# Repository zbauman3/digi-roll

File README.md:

# DigiRoll

A digital dice roller for D&D. Check out the docs site at https://zbauman3.github.io/digi-roll/

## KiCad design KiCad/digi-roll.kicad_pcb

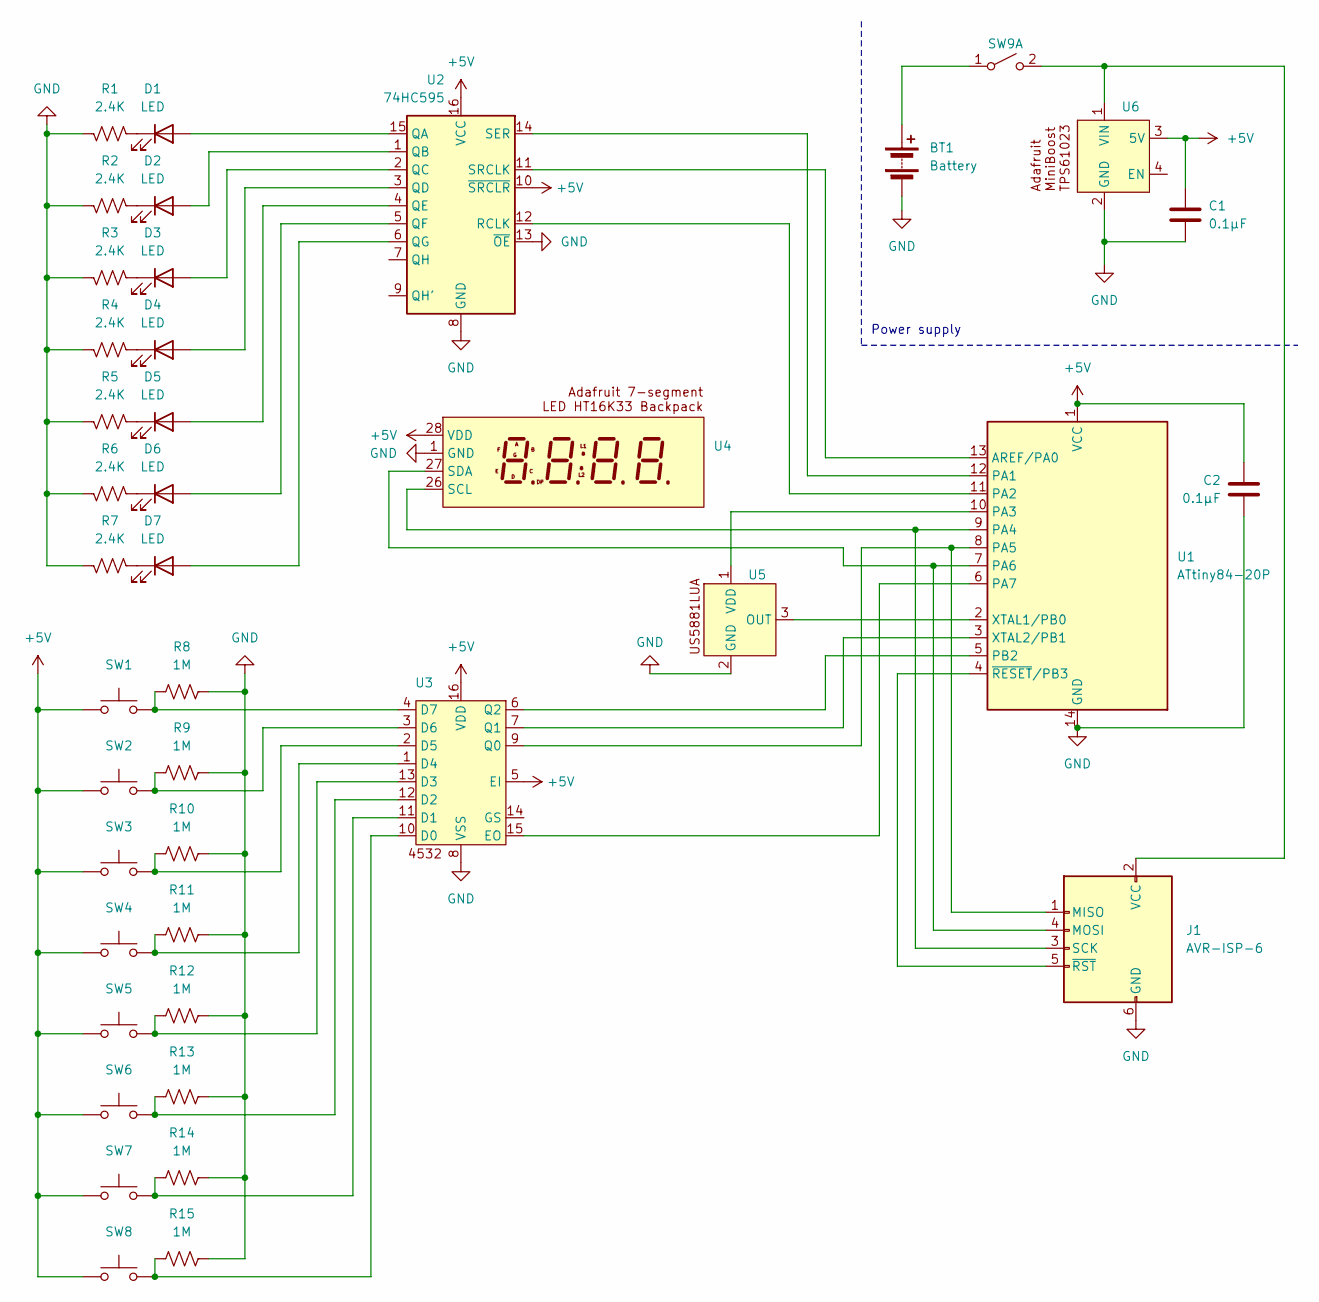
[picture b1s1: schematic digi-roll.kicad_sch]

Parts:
BT1: Battery; PinHeader_1x02_P2.54mm_Vertical
C1, C2: 0.1µF; C_Disc_D4.7mm_W2.5mm_P5.00mm
D1, D2, D3, D4, D5, D6, D7: LED; LED_D5.0mm
J1: AVR-ISP-6; PinHeader_2x03_P2.54mm_Vertical
R1, R2, R3, R4, R5, R6, R7: 2.4K; R_Axial_DIN0207_L6.3mm_D2.5mm_P7.62mm_Horizontal
R8, R9, R10, R11, R12, R13, R14, R15: 1M; R_Axial_DIN0207_L6.3mm_D2.5mm_P7.62mm_Horizontal
SW1, SW2, SW3, SW4, SW5, SW6, SW7, SW8: SW_MEC_5E; SW_PUSH_6mm_H5mm
SW9: SW_DPST_x2; PinHeader_1x02_P2.54mm_Vertical
U1: ATtiny84-20P; DIP-14_W7.62mm
U2: 74HC595; DIP-16_W7.62mm
U3: DIP-16_W7.62mm
U4: Adafruit_7_seg
U5: PinHeader_1x03_P2.54mm_Vertical
U6: Adafruit_Miniboost

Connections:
+5V: C1.1, C2.1, SW1.1, SW2.1, SW3.1, SW4.1, SW5.1, SW6.1, SW7.1, SW8.1, U1.1 (VCC), U2.10 (~SRCLR), U2.16 (VCC), U3.5 (EI), U3.16 (VDD), U4.28 (VDD), U6.3 (5V)
GND: BT1.2 (-), C1.2, C2.2, J1.6 (GND), R1.2, R2.2, R3.2, R4.2, R5.2, R6.2, R7.2, R8.2, R9.2, R10.2, R11.2, R12.2, R13.2, R14.2, R15.2, U1.14 (GND), U2.8 (GND), U2.13 (~OE), U3.8 (VSS), U4.1 (GND), U5.2 (GND), U6.2 (GND)
unnamed: BT1.1 (+), SW9.1 (A)
unnamed: D1.2 (A), U2.15 (QA)
unnamed: D1.1 (K), R1.1
unnamed: D2.2 (A), U2.1 (QB)
unnamed: D2.1 (K), R2.1
unnamed: D3.2 (A), U2.2 (QC)
unnamed: D3.1 (K), R3.1
unnamed: D4.2 (A), U2.3 (QD)
unnamed: D4.1 (K), R4.1
unnamed: D5.2 (A), U2.4 (QE)
unnamed: D5.1 (K), R5.1
unnamed: D6.2 (A), U2.5 (QF)
unnamed: D6.1 (K), R6.1
unnamed: D7.2 (A), U2.6 (QG)
unnamed: D7.1 (K), R7.1
unnamed: J1.1 (MISO), U1.8 (PA5), U3.9 (Q0)
unnamed: J1.4 (MOSI), U1.7 (PA6), U4.27 (SDA)
unnamed: J1.3 (SCK), U1.9 (PA4), U4.26 (SCL)
unnamed: J1.2 (VCC), SW9.2 (B), U6.1 (VIN)
unnamed: J1.5 (~RST), U1.4 (~RESET/PB3)
unnamed: U1.13 (AREF/PA0), U2.11 (SRCLK)
unnamed: U1.12 (PA1), U2.14 (SER)
unnamed: U1.11 (PA2), U2.12 (RCLK)
unnamed: U1.10 (PA3), U5.1 (VDD)
unnamed: U1.6 (PA7), U3.15 (EO)
unnamed: U1.5 (PB2), U3.6 (Q2)
unnamed: U1.2 (XTAL1/PB0), U5.3 (OUT)
unnamed: U1.3 (XTAL2/PB1), U3.7 (Q1)
unnamed: R15.1, SW8.2, U3.10 (D0)
unnamed: R14.1, SW7.2, U3.11 (D1)
unnamed: R13.1, SW6.2, U3.12 (D2)
unnamed: R12.1, SW5.2, U3.13 (D3)
unnamed: R11.1, SW4.2, U3.1 (D4)
unnamed: R10.1, SW3.2, U3.2 (D5)
unnamed: R9.1, SW2.2, U3.3 (D6)
unnamed: R8.1, SW1.2, U3.4 (D7)

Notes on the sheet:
Power supply

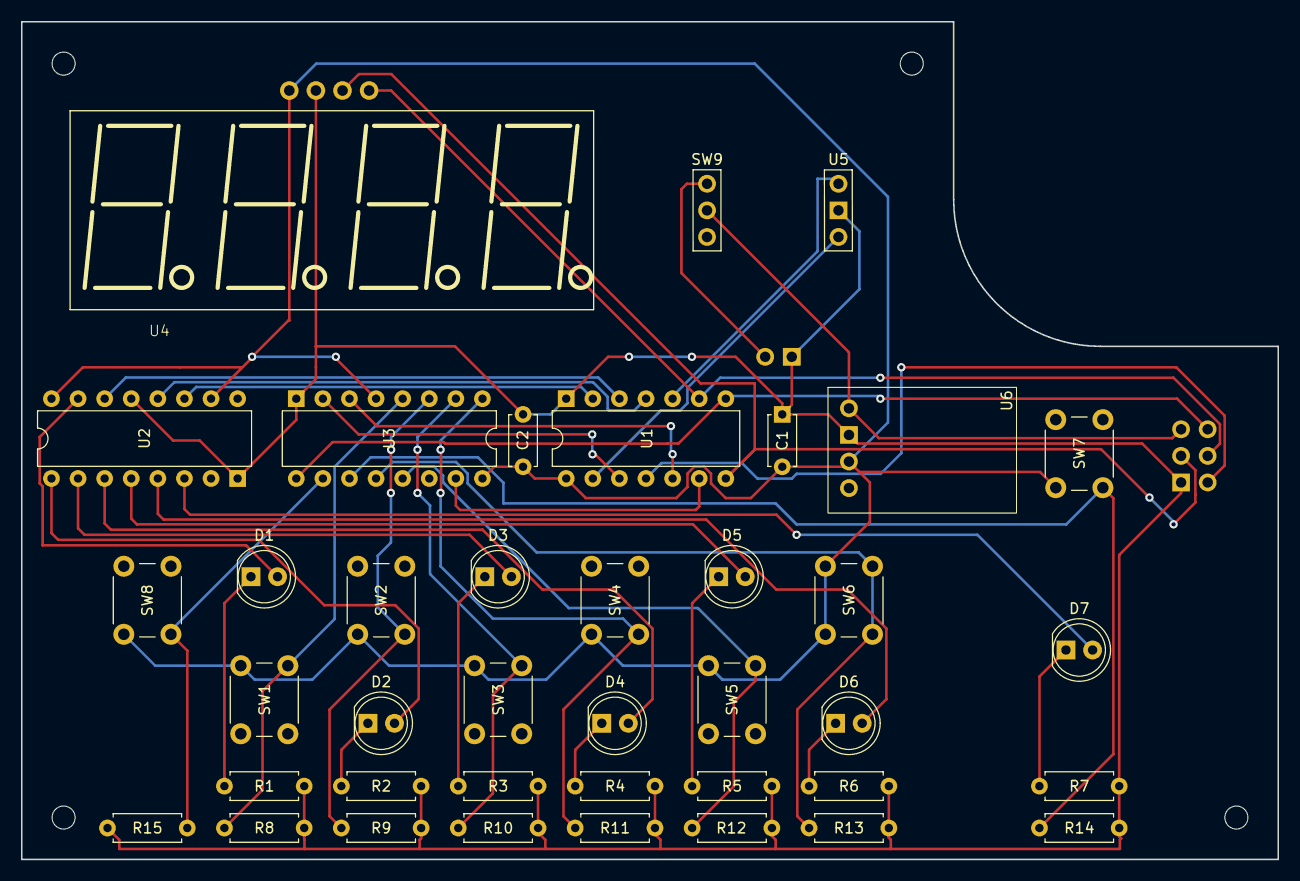
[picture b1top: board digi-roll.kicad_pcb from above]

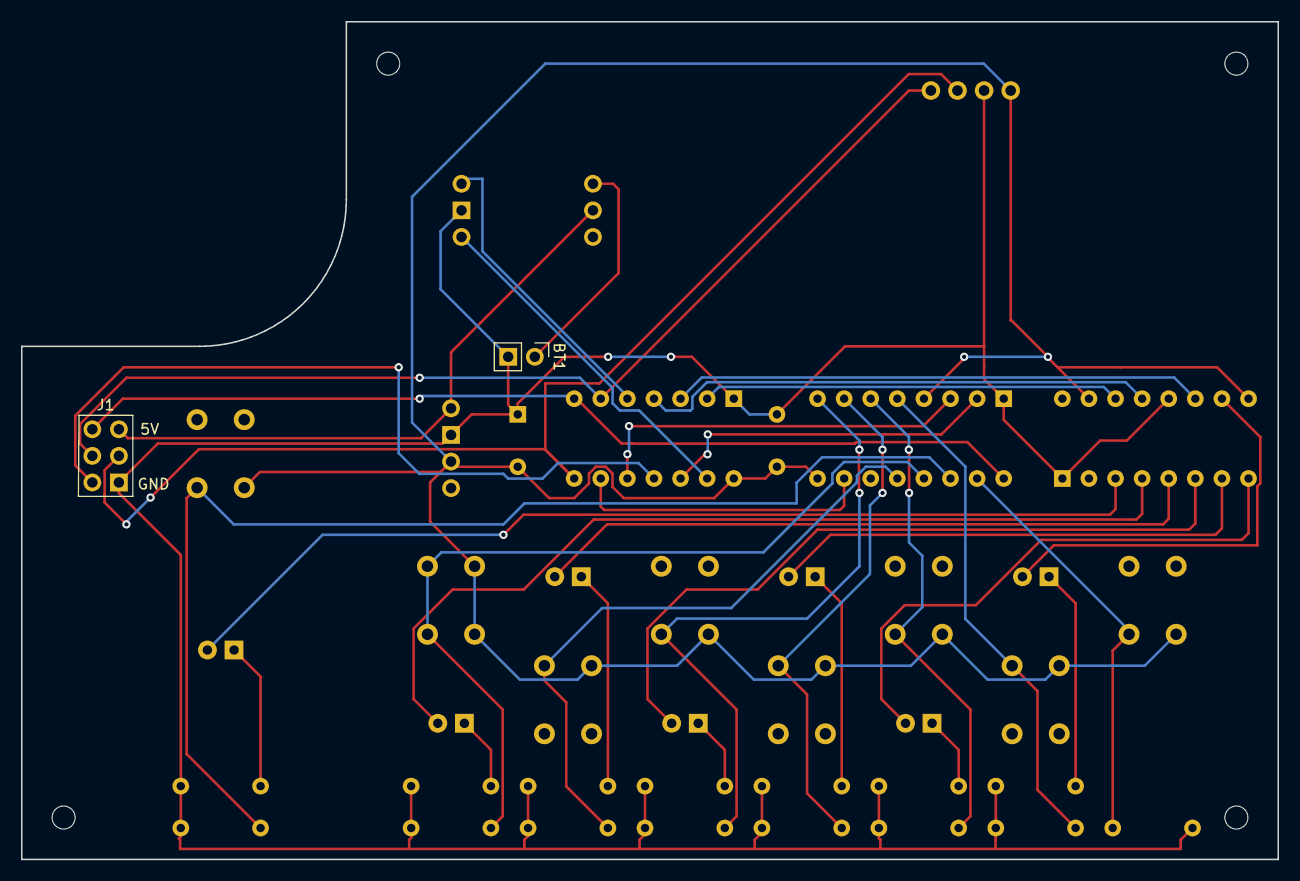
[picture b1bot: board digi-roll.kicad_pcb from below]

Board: 2 copper layers, 120.0 x 80.0 mm, 41 parts (2 on the bottom side), 38 nets.

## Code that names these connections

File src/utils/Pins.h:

#ifndef Z_PINS_H
#define Z_PINS_H

// ATMEL ATTINY84 / ARDUINO - COUNTERCLOCKWISE
//
//                           +-\/-+
//                     VCC  1|    |14  GND
//  HALL INT   (D  0)  PB0  2|    |13  PA0  (D 10)        LED SCK
//  BTN 1      (D  1)  PB1  3|    |12  PA1  (D  9)        LED DATA
//             (D 11)  PB3  4|    |11  PA2  (D  8)        LED RCLK
//  BTN 2      (D  2)  PB2  5|    |10  PA3  (D  7)        HALL EN
//  BTN INT    (D  3)  PA7  6|    |9   PA4  (D  6)        I2C SCL
//  I2C SDA    (D  4)  PA6  7|    |8   PA5  (D  5)        BTN 0
//

#define PIN_HALL_INT 0
#define PIN_HALL_INT_VECT PCINT1_vect
// setup the interrupt for the hall effect sensor
#define PIN_HALL_INT_SETUP()                                                   \
  GIMSK |= (1 << PCIE1);                                                       \
  PCMSK1 |= (1 << PCINT8)
// check if the hall effect sensor is currently triggering
#define PIN_HALL_INT_IS_ACTIVE() (!(PINB & _BV(PINB0)))
#define PIN_HALL_ENABLE 7

#define PIN_BTN_0 5
#define PIN_BTN_1 1
#define PIN_BTN_2 2
// read the buttons without using the arduino libs
#define PIN_BTN_0_READ() ((PINA & _BV(PINA5)) ? 1 : 0)
#define PIN_BTN_1_READ() ((PINB & _BV(PINB1)) ? 1 : 0)
#define PIN_BTN_2_READ() ((PINB & _BV(PINB2)) ? 1 : 0)

#define PIN_BTN_INT 3
#define PIN_BTN_INT_VECT PCINT0_vect
// setup the interrupt for the buttons
#define PIN_BTN_INT_SETUP()                                                    \
  GIMSK |= (1 << PCIE0);                                                       \
  PCMSK0 |= (1 << PCINT7)
// check if the buttons are currently triggering
#define PIN_BTN_INT_IS_PRESSING() (!(PINA & _BV(PINA7)))

#define PIN_LED_SCLK 10
#define PIN_LED_RCLK 8
#define PIN_LED_DATA 9

#endif // Z_PINS_H

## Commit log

2024-07-29 init
2024-07-31 init AceRoutine
2024-08-01 coroutine actions
2024-08-01 add 595 coroutine
2024-08-11 add models
2024-08-11 reset mode
2024-08-12 init buttons in interrupts
2024-08-12 abstract button presses
2024-08-13 dice select
2024-08-15 debounce
2024-08-17 cleanup buttons - cleanup state
2024-08-17 rename vars
2024-08-17 add brightness dimmer and idle timout
2024-08-17 add colon
2024-08-18 nearly done
2024-08-18 free up space by removing string usage
2024-08-18 finish display look
2024-08-18 remove test
2024-08-21 LED blinking
2024-08-21 move pins
2024-08-21 remove mode booleans
2024-08-21 cleanup
2024-08-21 bpj to enable/disable HALL for low power
2024-08-21 add sleep modes
2024-08-22 finish low power mode
2024-08-22 schema
2024-08-22 cleanup and comments
2024-08-22 add results sleep, reset _lastRolledAt, new display
2024-08-24 fix rng
2024-08-24 better button debouncing
2024-08-24 remove BPJ for HALL
2024-09-05 finish PCB order
2024-09-11 Update to match the hardware button order
2024-09-13 assets
2024-11-24 tune and 3d models
2024-11-26 init docs
2024-11-26 fix header
2024-11-27 work on site
2024-11-27 remove meta
2024-11-27 style cleanup
2024-11-27 import
2024-11-27 fix styles
2024-11-27 work on docs
2024-11-27 add cover
2024-11-27 github link
2024-11-28 docs
2024-12-01 fixes
2024-12-01 movie
2024-12-01 new photos
2024-12-01 change home image
2024-12-01 README
2024-12-09 usage docs
2024-12-16 Use atomic block and add sum
2024-12-16 add new sizes
